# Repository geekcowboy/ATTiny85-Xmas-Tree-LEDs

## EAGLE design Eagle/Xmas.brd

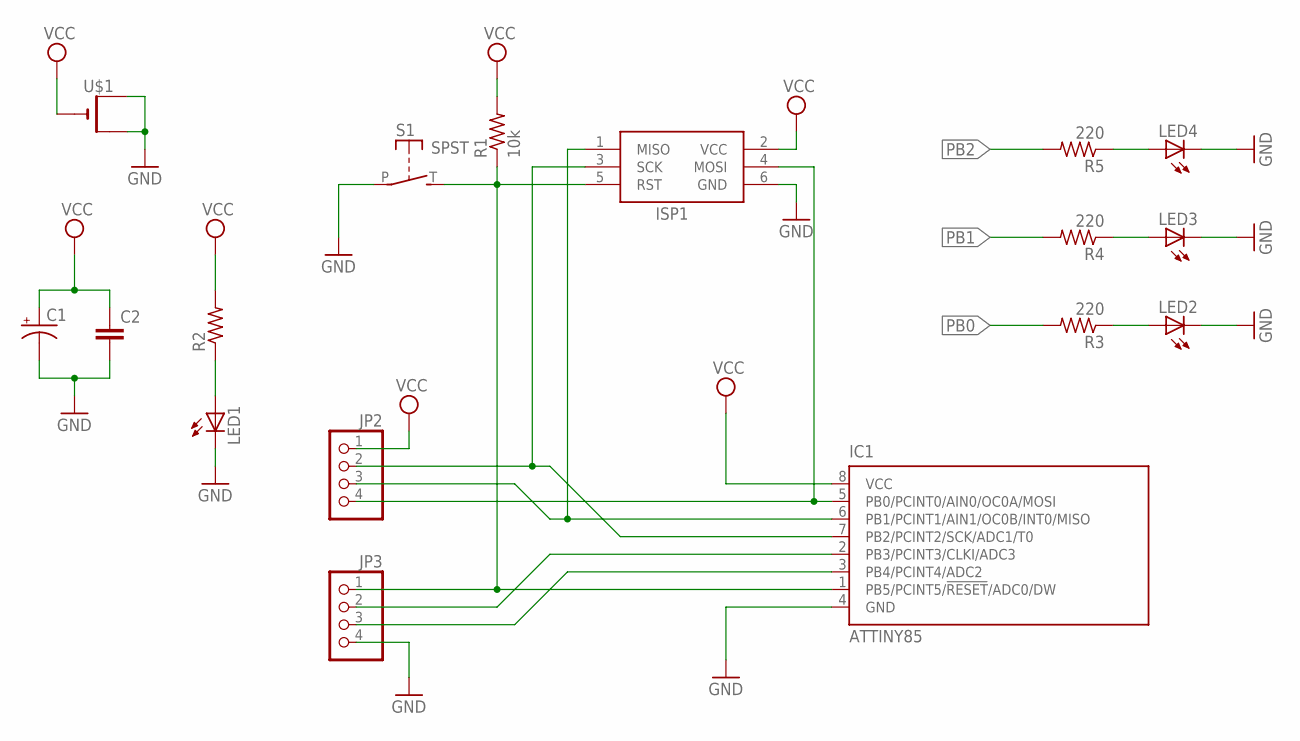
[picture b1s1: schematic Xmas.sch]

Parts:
C1: 100UF-25V-20%(PTH); CPOL-RADIAL-100UF-25V
C2: 0.1UF-50V-20%(PTH)KIT-EZ; CAP-PTH-SMALL-KIT
IC1: ATTINY85; DIL08
ISP1: AVRISP-6; AVRISP
JP2, JP3: PINHD-1X4; 1X04
LED1, LED2, LED3, LED4: LED3MM
R1: 10k; 0207/9
R2: R-US_0207/9; 0207/9
R3, R4, R5: 220; 0207/9
S1: SPST; JUDCOSPST
U$1: CR1220THM; CR1220-THM

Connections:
GND: C1.2 (-), C2.2, IC1.4 (GND), ISP1.6 (GND), JP3.4, LED1.K (C), LED2.K (C), LED3.K (C), LED4.K (C), S1.P, U$1.+1 (+), U$1.+2 (+1)
unnamed: LED1.A, R2.1
unnamed: LED2.A, R3.1
unnamed: LED3.A, R4.1
unnamed: LED4.A, R5.1
PB0: IC1.5 (PB0/PCINT0/AIN0/OC0A/MOSI), ISP1.4 (MOSI), JP2.4, R3.2
PB1: IC1.6 (PB1/PCINT1/AIN1/OC0B/INT0/MISO), ISP1.1 (MISO), JP2.3, R4.2
PB2: IC1.7 (PB2/PCINT2/SCK/ADC1/T0), ISP1.3 (SCK), JP2.2, R5.2
PB3: IC1.2 (PB3/PCINT3/CLKI/ADC3), JP3.2
PB4: IC1.3 (PB4/PCINT4/ADC2), JP3.3
PB5: IC1.1 (PB5/PCINT5/!RESET!/ADC0/DW), ISP1.5 (RST), JP3.1, R1.1, S1.T (S)
VCC: C1.1 (+), C2.1, IC1.8 (VCC), ISP1.2 (VCC), JP2.1, R1.2, R2.2, U$1.-

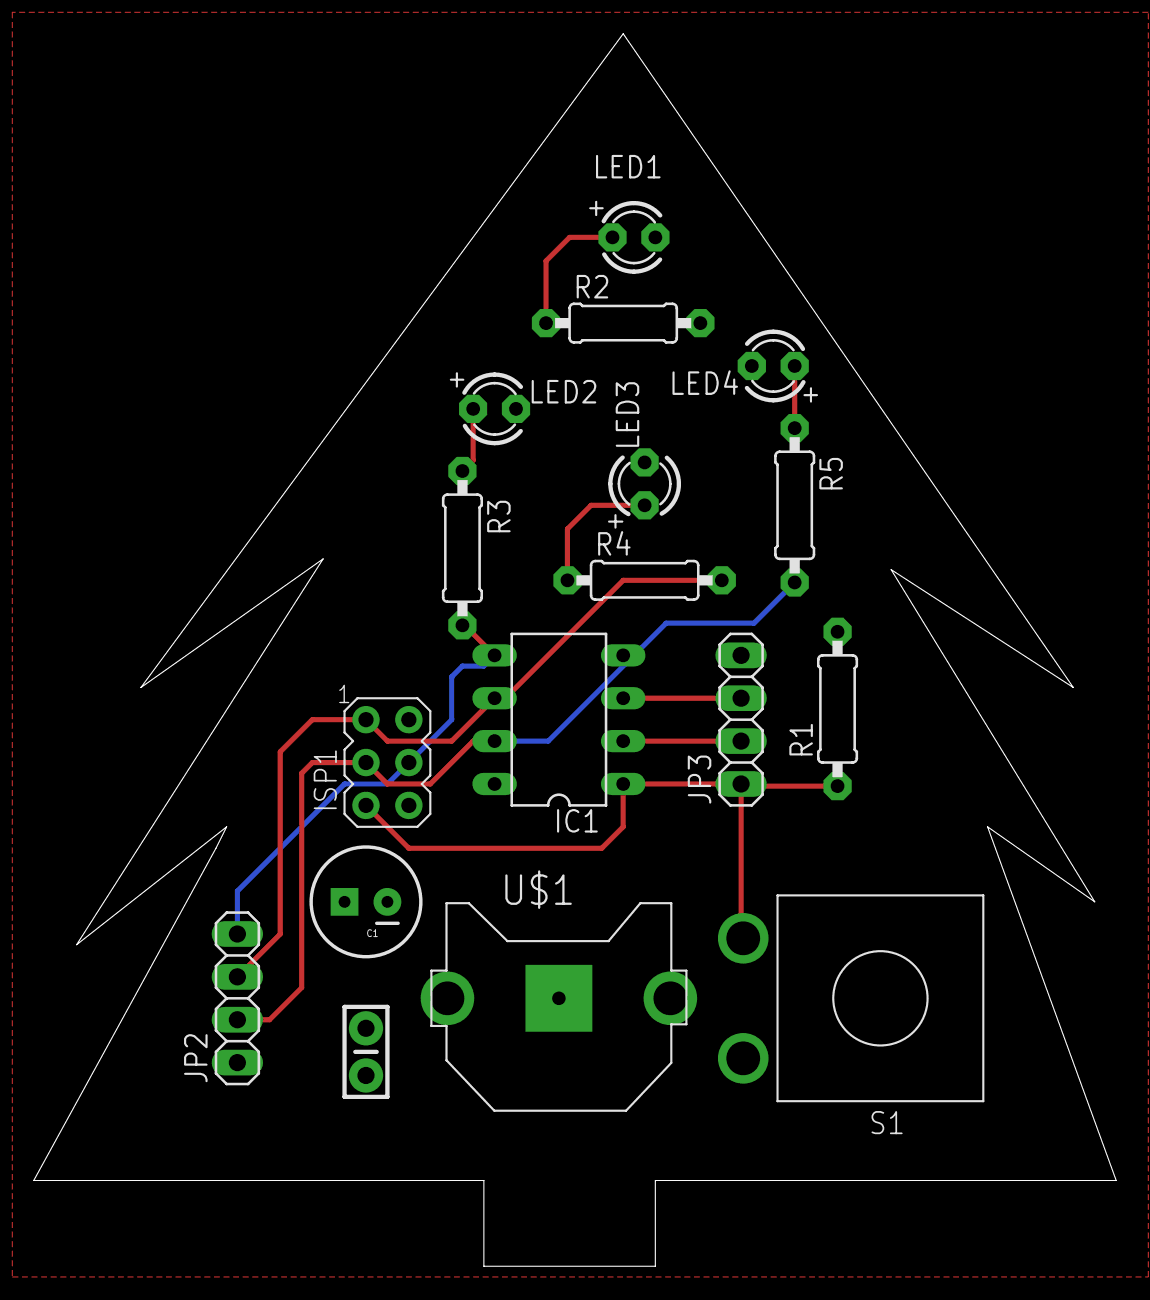
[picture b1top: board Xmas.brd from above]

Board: 2 copper layers, 64.1 x 73.0 mm, 17 parts (0 on the bottom side), 12 nets.

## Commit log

2015-11-01 Init commit

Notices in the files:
parts and their libraries:
SparkFun-Capacitors: Licensing: Creative Commons ShareAlike 4.0 International - https://creativecommons.org/licenses/by-sa/4.0
